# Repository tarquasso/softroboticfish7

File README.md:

***** SETUP *****  
-- This folder should be called /home/pi/softroboticfish7  

===== fish =====  
-- contains code that goes on the Pi in the fish and on the mbed in the fish  

===== controller =====  
-- contains code that goes on the Pi in the acoustic transmitter module (omitted for now in v7)

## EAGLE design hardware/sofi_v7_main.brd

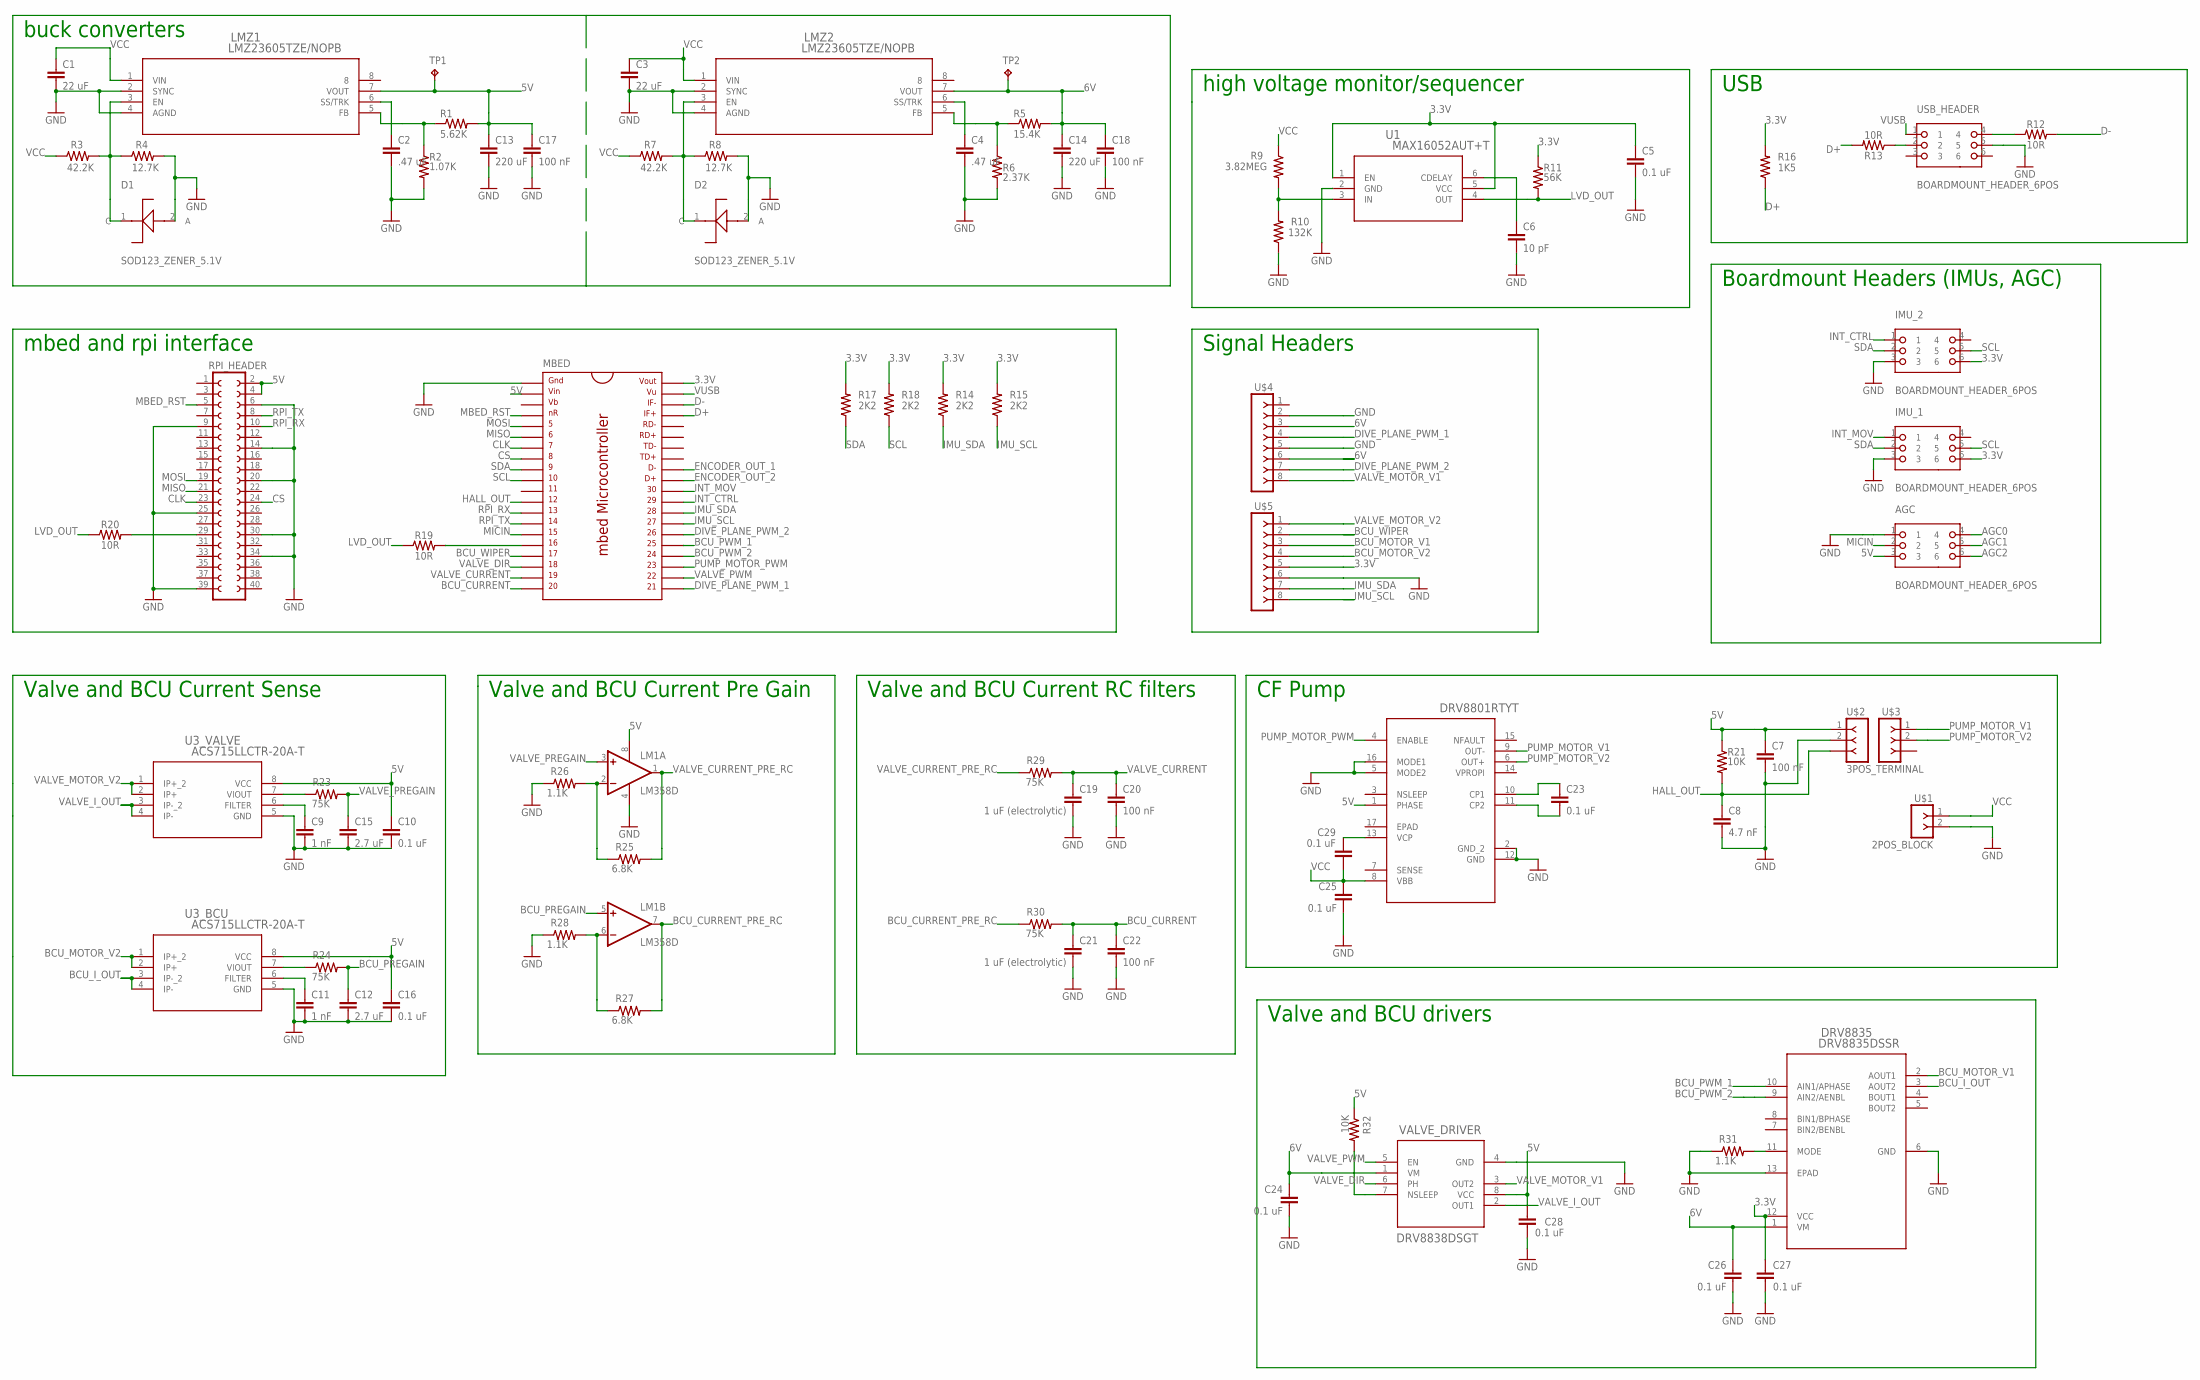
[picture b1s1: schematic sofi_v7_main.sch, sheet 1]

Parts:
AGC: BOARDMOUNT_HEADER_6POS; BOARDMOUNT_HEADER
C1, C3: 22 uF; C0805
C2, C4: .47 uF; C0805
C5, C23, C29: 0.1 uF; C0805
C6: 10 pF; C0603
C7, C17, C18, C20, C22: 100 nF; C0805
C8: 4.7 nF; C0805
C9, C11: 1 nF; C0603
C10, C16, C24, C25, C26, C27, C28: 0.1 uF; C0603
C12, C15: 2.7 uF; C0603
C13, C14: 220 uF; C1206
C19, C21: 1 uF (electrolytic); C0603
D1, D2: SOD123_ZENER_5.1V; SOD123_ZENER
DRV8801: DRV8801RTYT; RTY16
DRV8835: DRV8835DSSR; DSS12_P9X2
IMU_1, IMU_2: BOARDMOUNT_HEADER_6POS; BOARDMOUNT_HEADER
LM1: LM358D; SO08
LMZ1, LMZ2: LMZ23605TZE/NOPB; TZA07A
MBED: MBED_MICROCONTROLLER; DIL40_0.9
R1: 5.62K; M0805
R2: 1.07K; M0805
R3, R7: 42.2K; M0805
R4, R8: 12.7K; M0805
R5: 15.4K; M0805
R6: 2.37K; M0805
R9: 3.82MEG; 0603
R10: 132K; 0603
R11: 56K; R0603
R12, R13, R19, R20: 10R; 0603
R14, R15, R17, R18: 2K2; 0603
R16: 1K5; 0603
R21, R32: 10K; M0805
R23, R24, R29, R30: 75K; M0805
R25, R27: 6.8K; M0805
R26, R28, R31: 1.1K; M0805
RPI_HEADER: FE20-2
TP1, TP2: TPB1,27; B1,27
U1: MAX16052AUT+T; 21-0058I
U3_BCU, U3_VALVE: ACS715LLCTR-20A-T; SOIC-8
U$1: 2POS_BLOCK
U$2, U$3: 3POS_TERMINAL
U$4, U$5: 8POS_TERMINAL
USB_HEADER: BOARDMOUNT_HEADER_6POS; BOARDMOUNT_HEADER
VALVE_DRIVER: DRV8838DSGT; DSG8_P9X1P6

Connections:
3.3V: C5.1, C27.1, DRV8835.12 (VCC), IMU_1.6, IMU_2.6, MBED.40, R11.1, R14.2, R15.2, R16.2, R17.2, R18.2, U1.1 (EN), U1.5 (VCC), U$5.5
5V: AGC.3, C7.1, C10.1, C13.1, C16.1, C17.1, C28.1, DRV8801.1 (PHASE), LM1.8 (V+), LMZ1.7 (VOUT), MBED.2, R1.2, R21.1, R32.1, RPI_HEADER.2, RPI_HEADER.4, TP1.TP, U3_BCU.8 (VCC), U3_VALVE.8 (VCC), U$2.1, VALVE_DRIVER.8 (VCC)
6V: C14.1, C18.1, C24.1, C26.1, DRV8835.1 (VM), LMZ2.7 (VOUT), R5.2, TP2.TP, U$4.3, U$4.6, VALVE_DRIVER.1 (VM)
AGC0: AGC.4
AGC1: AGC.5
AGC2: AGC.6
BCU_CURRENT: C21.1, C22.1, MBED.20, R30.2
BCU_CURRENT_PRE_RC: LM1.7 (OUT), R27.2, R30.1
BCU_I_OUT: DRV8835.3 (AOUT2), U3_BCU.3 (IP-_2), U3_BCU.4 (IP-)
BCU_MOTOR_V1: DRV8835.2 (AOUT1), U$5.3
BCU_MOTOR_V2: U3_BCU.1 (IP+_2), U3_BCU.2 (IP+), U$5.4
BCU_PREGAIN: C12.1, LM1.5 (+IN), R24.2
BCU_PWM_1: DRV8835.10 (AIN1/APHASE), MBED.25
BCU_PWM_2: DRV8835.9 (AIN2/AENBL), MBED.24
BCU_WIPER: MBED.17, U$5.2
CLK: MBED.7, RPI_HEADER.23
CS: MBED.8, RPI_HEADER.24
D+: MBED.37, R13.2, R16.1
D-: MBED.38, R12.2
DIVE_PLANE_PWM_1: MBED.21, U$4.4
DIVE_PLANE_PWM_2: MBED.26, U$4.7
ENCODER_OUT_1: MBED.32
ENCODER_OUT_2: MBED.31
GND: AGC.1, C1.2, C2.2, C3.2, C4.2, C5.2, C6.2, C7.2, C8.2, C9.2, C10.2, C11.2, C12.2, C13.2, C14.2, C15.2, C16.2, C17.2, C18.2, C19.2, C20.2, C21.2, C22.2, C24.2, C25.2, C26.2, C27.2, C28.2, D1.2 (A), D2.2 (A), DRV8801.2 (GND_2), DRV8801.5 (MODE2), DRV8801.12 (GND), DRV8801.16 (MODE1), DRV8835.6 (GND), DRV8835.13 (EPAD), IMU_1.3, IMU_2.3, LM1.4 (V-), LMZ1.2 (SYNC), LMZ1.4 (AGND), LMZ2.2 (SYNC), LMZ2.4 (AGND), MBED.1, R2.2, R4.2, R6.2, R8.2, R10.1, R26.1, R28.1, R31.1, RPI_HEADER.6, RPI_HEADER.9, RPI_HEADER.14, RPI_HEADER.20, RPI_HEADER.25, RPI_HEADER.30, RPI_HEADER.34, RPI_HEADER.39, U1.2 (GND), U3_BCU.5 (GND), U3_VALVE.5 (GND), U$1.2, U$2.2, U$4.2, U$4.5, U$5.6, USB_HEADER.5, VALVE_DRIVER.4 (GND)
HALL_OUT: C8.1, MBED.12, R21.2, U$2.3
IMU_SCL: MBED.27, R15.1, U$5.8
IMU_SDA: MBED.28, R14.1, U$5.7
INT_CTRL: IMU_2.1, MBED.29
INT_MOV: IMU_1.1, MBED.30
LVD_OUT: R11.2, R19.1, R20.1, U1.4 (OUT)
MBED_RST: MBED.4, RPI_HEADER.5
MICIN: AGC.2, MBED.15
MISO: MBED.6, RPI_HEADER.21
MOSI: MBED.5, RPI_HEADER.19
unnamed: R20.2, RPI_HEADER.29
unnamed: C23.1, DRV8801.10 (CP1)
unnamed: LMZ1.5 (FB), R1.1, R2.1
unnamed: R9.2, R10.2, U1.3 (IN)
unnamed: D1.1 (C), LMZ1.3 (EN), R3.2, R4.1
unnamed: C4.1, LMZ2.6 (SS/TRK)
unnamed: LMZ2.5 (FB), R5.1, R6.1
unnamed: C2.1, LMZ1.6 (SS/TRK)
unnamed: C6.1, U1.6 (CDELAY)
unnamed: D2.1 (C), LMZ2.3 (EN), R7.2, R8.1
unnamed: R23.1, U3_VALVE.7 (VIOUT)
unnamed: C9.1, U3_VALVE.6 (FILTER)
unnamed: MBED.16, R19.2
unnamed: R24.1, U3_BCU.7 (VIOUT)
unnamed: C11.1, U3_BCU.6 (FILTER)
unnamed: C23.2, DRV8801.11 (CP2)
unnamed: C29.1, DRV8801.13 (VCP)
unnamed: LM1.2 (-IN), R25.1, R26.2
unnamed: R12.1, USB_HEADER.4
unnamed: LM1.6 (-IN), R27.1, R28.2
unnamed: R13.1, USB_HEADER.2
unnamed: DRV8835.11 (MODE), R31.2
unnamed: R32.2, VALVE_DRIVER.7 (NSLEEP)
PUMP_MOTOR_PWM: DRV8801.4 (ENABLE), MBED.23
PUMP_MOTOR_V1: DRV8801.9 (OUT-), U$3.1
PUMP_MOTOR_V2: DRV8801.6 (OUT+), U$3.2
RPI_RX: MBED.13, RPI_HEADER.10
RPI_TX: MBED.14, RPI_HEADER.8
SCL: IMU_1.5, IMU_2.5, MBED.10, R18.1
SDA: IMU_1.2, IMU_2.2, MBED.9, R17.1
SENSE: DRV8801.7 (SENSE)
VALVE_CURRENT: C19.1, C20.1, MBED.19, R29.2
VALVE_CURRENT_PRE_RC: LM1.1 (OUT), R25.2, R29.1
VALVE_DIR: MBED.18, VALVE_DRIVER.6 (PH)
VALVE_I_OUT: U3_VALVE.3 (IP-_2), U3_VALVE.4 (IP-), VALVE_DRIVER.2 (OUT1)
VALVE_MOTOR_V1: U$4.8, VALVE_DRIVER.3 (OUT2)
VALVE_MOTOR_V2: U3_VALVE.1 (IP+_2), U3_VALVE.2 (IP+), U$5.1
VALVE_PREGAIN: C15.1, LM1.3 (+IN), R23.2
VALVE_PWM: MBED.22, VALVE_DRIVER.5 (EN)
VCC: C1.1, C3.1, C25.1, C29.2, DRV8801.8 (VBB), LMZ1.1 (VIN), LMZ2.1 (VIN), R3.1, R7.1, R9.1, U$1.1
VUSB: MBED.39, USB_HEADER.1

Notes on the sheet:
mbed and rpi interface
buck converters
high voltage monitor/sequencer
Valve and BCU Current RC filters
Valve and BCU Current Pre Gain
Valve and BCU Current Sense
Signal Headers
USB
CF Pump
Valve and BCU drivers
Boardmount Headers (IMUs, AGC)

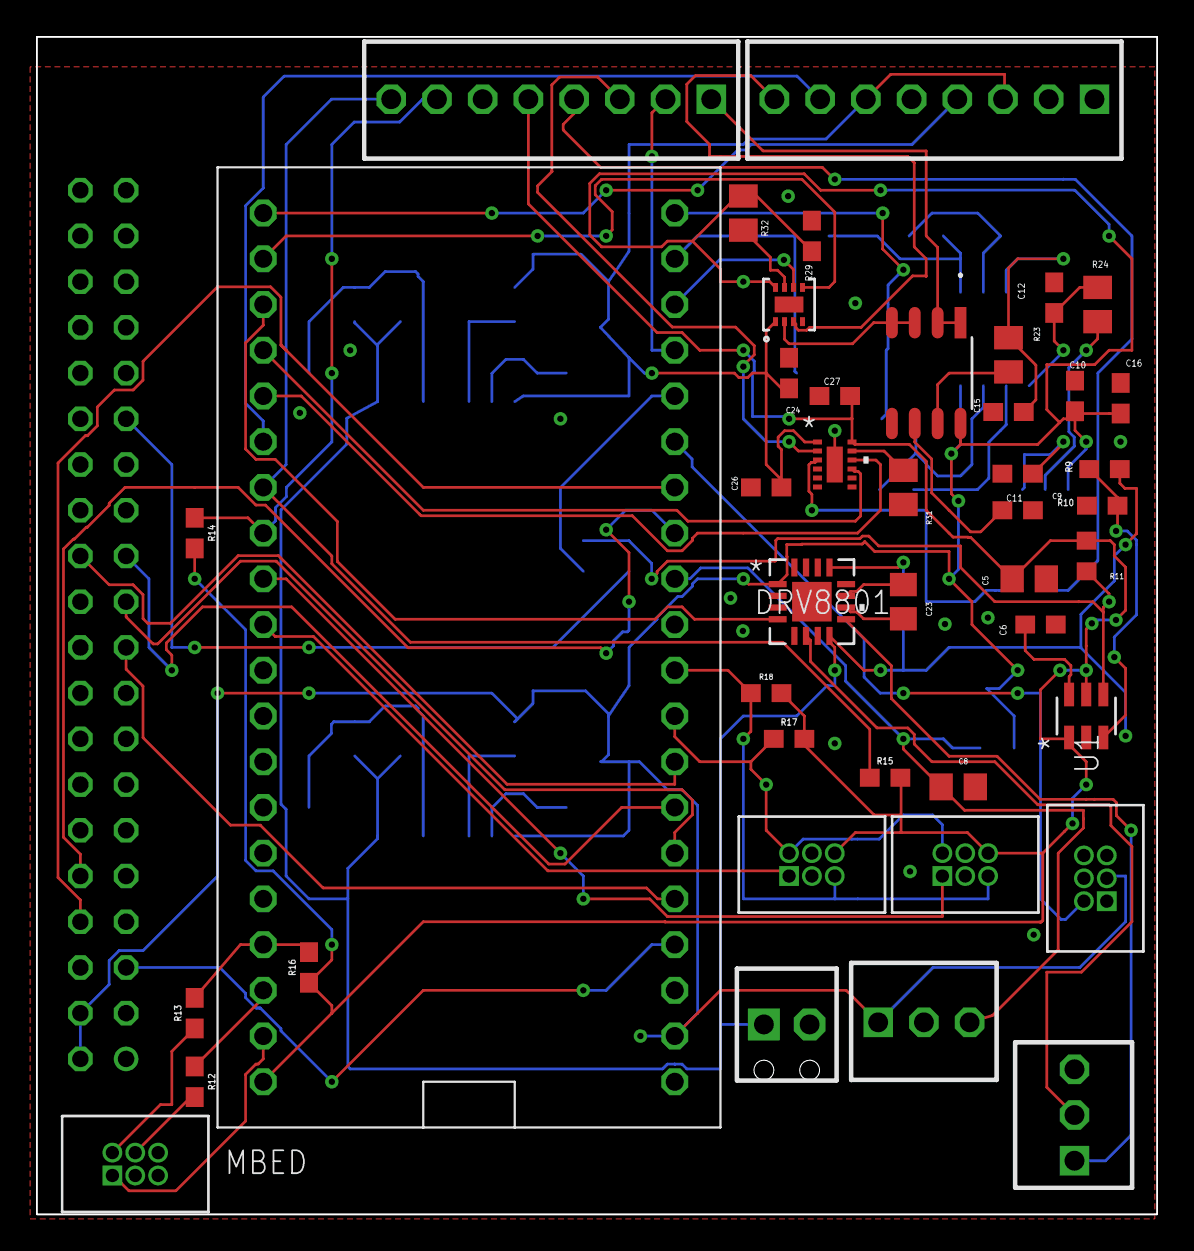
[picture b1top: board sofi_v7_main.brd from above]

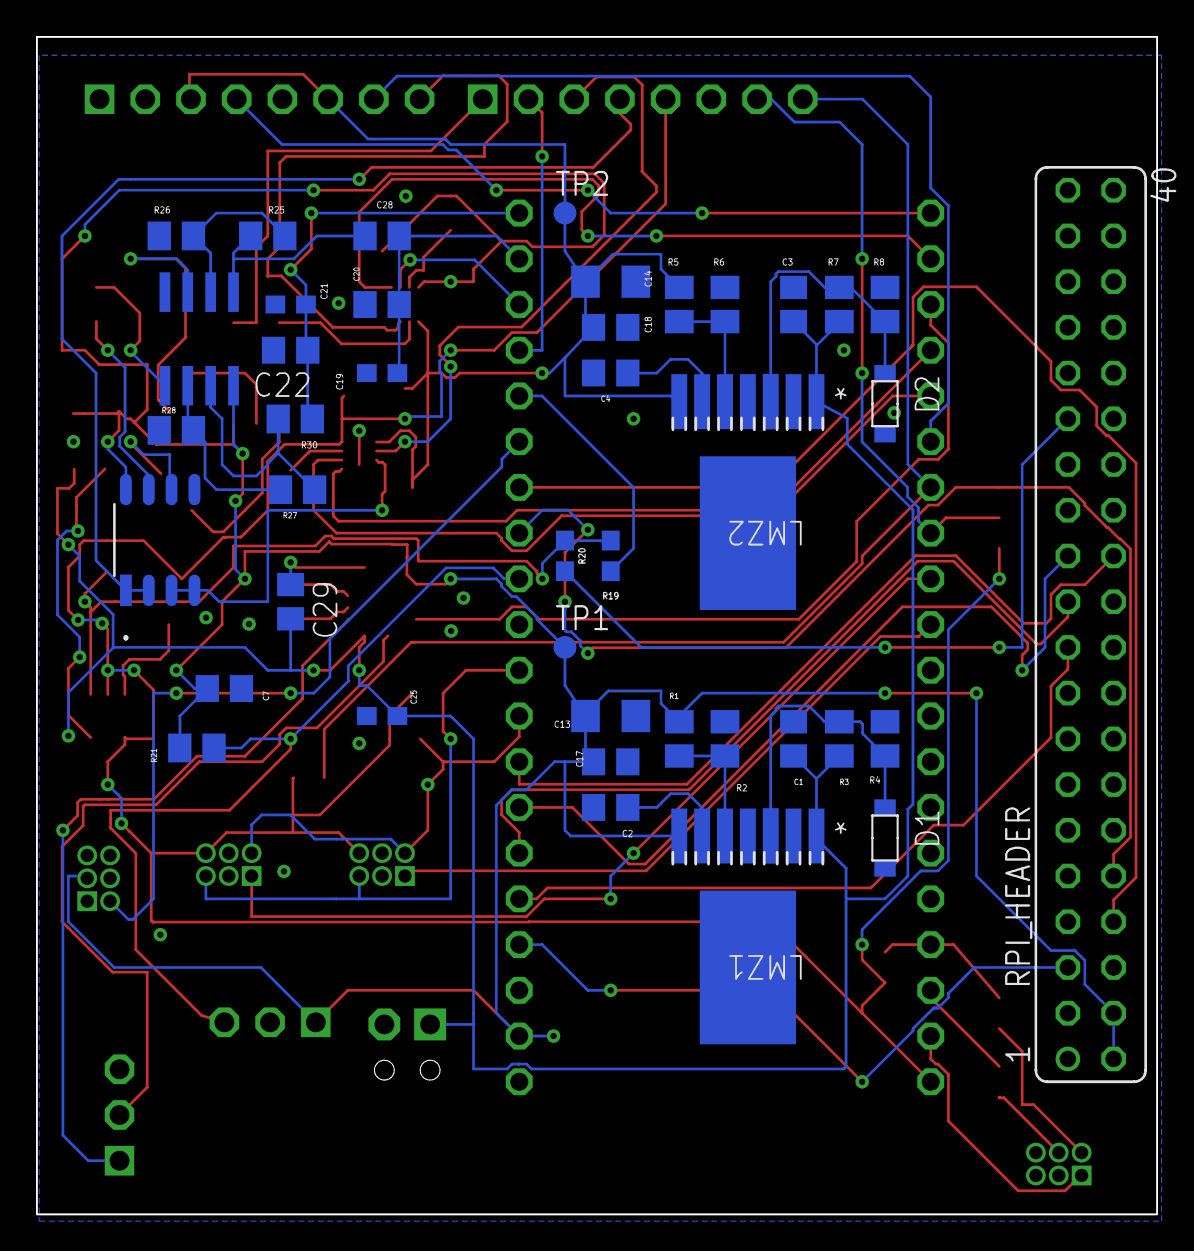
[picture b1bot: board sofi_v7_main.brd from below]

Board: 2 copper layers, 62.2 x 65.4 mm, 84 parts (41 on the bottom side), 69 nets.

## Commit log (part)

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2016-03-05 set up skeleton catkin workspace directory and imported relevant files from softroboticfish4 (but did not yet convert old code to new system setup)
2016-03-08 connected joystick to produce depth, yaw, and speed inputs
2016-03-08 added actual launch and node files
2016-03-12 added freq_ctrl to joystick commands; serial communication functional to light LEDs based on commands in
2016-03-13 switched joystick axes inputs from left is positive to left is negative; removed unused files from fish4_code
2016-03-13 remove .hg folder
2016-03-13 add project file for project
2016-03-14 added lpc expresso project properly, so it can now be imported elsewhere
2016-03-14 added initial versions of BCU and Valve control classes - code compiles but has some warnings; FishController is updated accordingly; ROSControl files in mbed folder is updated but not merged into mb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
2016-03-17 Moving #defines that control modality into individual h files Avoids singleton creation when modalities are disabled
2016-03-17 Adding saved bin files from important experiments
2016-03-18 Adding pi scripts such as volume and view/kill fish processes
2016-03-18 Adding rx startup scripts
2016-03-18 Adding RX python scripts
2016-03-18 Organizing and restructuring all files
2016-03-18 Making scripts executable
2016-03-18 Updating Pi scripts
2016-03-18 Editing readme files to try to have github show line breaks
2016-03-18 make debug build on mbed
2016-03-19 activate serial controller, deactivate acoustic controller
2016-03-19 Refactor FishController to searate fish 4 and fish 6
2016-03-19 - reimplemented valve with pump control - version based on cyndia's approach. this approach saturates - changed name of bcu class
2016-03-19 PumpWithValve: updated yaw method
2016-03-19 add imu and pressure sensor
2016-04-13 added basic tests for valve (freq and yaw input) and bcu to move motors based on keyboard commands and hall/pressure sensor readings
2016-05-01 added project to experiment with BCU input voltage and resultant motor current & encoder positions made superficial changes to PumpWithValve class added PID control loops via pressure and encoder sen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
2016-05-04 added base timing test for just the pressure sensor (BCU_Test/main.cpp); test for the BCU moved to main_real.txt finished testing the added failsafe for the Valve
2016-06-10 adding header files for msgs
2016-06-10 fixed a lot about depth_control
2016-06-15 Added very basic IMU Test
2016-06-16 first commit for branch. Tried to bring in the last couple changes to master into dev, as well as a basic IMU_Test.
2016-06-20 Added basic serial bin for mbed. Counts down binary and sends BOOM string via rosserial
2016-06-21 Fixed folder structure of basic serial test
2016-06-27 trying to fix CMakeLists in the old ros
2016-06-27 fixing dependencies
2016-06-27 fixed dep with depthcontrol
2016-06-27 whoops. fixed Cmake portion of dep issue with depth control
2016-06-28 first compile attempt
2016-06-28 fixed defaults
2016-06-28 improved gitignore
2016-06-28 improved gitignore again
2016-06-28 add gcc ar o files
2016-06-28 hopefully fixed axes issue
2016-06-28 fixed modes
2016-06-28 fixed axes
2016-06-28 fixed last mode
2016-06-28 add gitignnore
2016-06-28 libraries for buoyancy control unit
2016-06-28 main files for buyancy control unit
2016-06-28 lpc expresso mbed folder
2016-06-28 add ing project files for lpcex
2016-06-28 add gitignore
2016-06-29 working mbed side of depth test
2016-06-29 remove some unnecessary files
2016-06-29 updated project files
2016-06-29 remove more debug files
2016-06-30 Position control working
2016-06-30 Cleaned up
2016-06-30 cleanup
2016-06-30 add MODSERIAL to buyancy test unit
2016-06-30 add serialcomm and modeserial to buoyancy test
2016-06-30 remove ros lib release
2016-06-30 remove unnecessary files
2016-06-30 commit line ending changes
2016-06-30 add gitignore to roboticfish6
2016-06-30 update project file
2016-06-30 fix depth test to compile
2016-06-30 make depth test compilable in lpcexpresso
2016-06-30 Made ticker to work with potentiometer controls for gains
2016-07-01 BTU changes for memeber variabkle renaming
2016-07-01 renaming #defines
2016-07-01 serial comm addition
2016-07-01 update modserial
2016-07-01 set up for testing
2016-07-01 Non static single ticker version of the btu, ready for plugin.
2016-07-01 buoyancy test unit now linking to static lib
2016-07-01 added servo option and depth to pressure conversion
2016-07-01 remove libs from depth test
2016-07-02 minor calculation fix
2016-07-03 buoyancy_test_unit_servo
2016-07-03 add btu to libs
2016-07-03 updated bcu test projects
2016-07-03 btu servo release version compiles
2016-07-03 add position reading and store position value to servo class
2016-07-03 calibrated position controller for btu
2016-07-04 working on pressure sensor reading, mbed not starting up
2016-07-04 updated project settings
2016-07-04 remove waits from MS5837 pressure unit library
2016-07-04 add time step minimum
2016-07-05 created call to controller.
2016-07-05 cleared out BTU folder in Depth_Test
2016-07-05 add bias to make the pid controller workable
2016-07-05 added security to pressure sensor
2016-07-05 set value to zero and add printf to the main
2016-07-05 btu: get pressure reading at start
2016-07-05 ready for second pool test
2016-07-05 code used for experiment
2016-07-05 Added anti-reset-windup to compute()
2016-07-06 Added anti-reset windup
2016-07-06 changed depth_test to use new BTU lite
2016-07-06 fixed bad naming, calls of getPressureReading
2016-07-06 fixed encapsulation of btu lite
2016-07-07 fixed several bugs in PID, BTU
2016-07-07 fixed scaling on rpi side
2016-07-07 fixed default mode on pi side
2016-07-07 working pcSerial based test
2016-07-07 working buoyancy test for pool
2016-07-07 updated servo values
2016-07-08 added serial logging scripts
2016-07-08 last minute improvement in logging
2016-07-11 added mission mode code
2016-07-11 started writing for Actuator
2016-07-11 added logging
2016-07-12 made multi depth missions work
2016-07-13 fixed various bugs in mission control
2016-07-13 pool ready mission control
2016-07-14 fixed no debrief after timeout bug
2016-07-14 pool ready mission btu
2016-07-15 project files
2016-07-15 added SMA filter and mission code for actuator
2016-07-15 better default value
2016-07-18 small updates
2016-07-18 update mbed libs cproject
2016-07-19 fixed printf
2016-07-19 added master-slave to BtuLinear. Commented out clip
2016-07-19 fixed naming problems
2016-07-19 fix project warnings for missing include paths
2016-07-19 moving window temp removed
2016-07-19 fixed vel control edge cases'
2016-07-19 make time step 3 times the pressure sensor time step fix moving average pointer bug
2016-07-19 pressure sensor working
2016-07-19 remove binary
2016-07-19 add #defines
2016-07-19 clipped commandable voltage
2016-07-19 doing some cleanup, reorganization
2016-07-19 more cleanup
2016-07-19 moved BCU_Test to Deprecated
2016-07-19 shifting around folders
2016-07-19 completing the shuffle
2016-07-19 cleared up IMU_Test moving
2016-07-20 updated btu code
2016-07-20 remove pi_clip and replace with utility
2016-07-20 only reformat PID Controller code, no functionality change
2016-07-20 fix gain names in PID Controller cLASS
2016-07-20 update utility
2016-07-20 speed up compute step of PID Controller
2016-07-20 fix minor bug with btu linear
2016-07-20 rename variables in PID Controller
2016-07-21 set position control to use voltage
2016-07-21 add position control code using voltage
2016-07-21 depth controller now velocity based
2016-07-21 moved clipping and other checks to voltage control
2016-07-21 voltage control using correct updated variable for command now
2016-07-21 rename two local variables
2016-07-21 changing back to local floats
2016-07-21 changing back to local floats (reverted from commit af8a5c95ca4f8792d58ba17b3be1e454d5687c94)
2016-07-21 BtuLinear with Actuator class
2016-07-21 fixed wrong name for getting tunings within the main.cpp files of mission control and actuator control
2016-07-21 fixed tuning names to be consistent witrh nomenclature
2016-07-21 added dry run support
2016-07-21 compiling version of dry run support
2016-07-21 commented actuator code
2016-07-21 first draft of btu_act_combo. Compiles, but is untested
2016-07-21 code changes from experiment
2016-07-22 changed potentiometer pin
2016-07-22 add gitignores
2016-07-22 add position controller tunings
2016-07-22 reformatting code
2016-07-22 actuator class with moving average and simplified position min max
2016-07-22 working btu_act_combo
2016-07-22 fixed loop freezing issue
2016-07-22 added cyclic actuator test project and library file
2016-07-25 add gitignor for cycliuca ctuator
2016-07-25 add ref for cyclic actuator
2016-07-26 tweaked PID Position controller so it goes smoothly to the boundaries
2016-07-28 added script to debug hardware. also debugging scanf, printf
2016-07-28 changed velocity to voltage control
2016-07-28 good log with good gains
2016-08-01 added logs and curating script
2016-08-01 added the pool logs from today
2016-08-02 plotted pool testing and negated depth error
2016-08-02 cleaned up log folders a bit
2016-08-08 updated linear libraries and added servo version
2016-08-08 fixed a lot of rosserial stuff
2016-08-08 fixed depth control bug
2016-08-12 prepped for vv control
2016-08-17 pump AM control added
2016-08-17 loggssss
2016-08-22 added javadoc style docs to Btu
2016-08-23 fixes
2016-08-25 control for whole fish
2016-09-06 for pool test, accel control
2016-10-27 opencv links with camera package
2016-11-02 Camera pub and sub working
2016-11-04 Tested camera successfully with avg RGB values
2016-11-14 Camera driver
2016-12-09 fixed raspicam speed
2017-01-11 pin vor valve changes
2017-01-12 gitignore for compiled files; remove ros_lib
2017-01-12 Removed old camera package
2017-01-17 Revert rosserial_test to use existing msg
2017-01-17 No longer track build files for serial_test
2017-01-17 gitignore built files
2017-01-18 Fix bug in quaternion constructor
2017-01-18 Remove temperature to save buffer space
2017-01-18 Increase baud rate
2017-01-20 IMU test with new library, uses gcc4mbed
2017-01-23 Library to coordinate asynchronous access to I2C
2017-01-23 updated imu_test
2017-01-23 I2CManager can send command bytes; pressure sensor library uses I2CManager; test updated
2017-01-23 Removed serial print from I2CManager
2017-01-23 MBED collects IMU and pressure data simultaneously and publishes over ROS
2017-01-26 Apriltags library doesn't need to flip
2017-01-31 Minimal camera pipeline package
2017-03-16 OpenCV subdivided thresholding tester
2017-03-16 Matlab scripts to generate HSV histogram and print as a c array literal
2017-03-21 Added reference caps from videos, relevant crops
2017-03-21 Added relevant crops
2017-03-23 Updated corner detection algorithm
2017-04-13 Removed hard-coded pathnames; added instructions for running the line detection script
2019-06-24 Rename sofi_v7_main.brd to hardware/sofi_v7_main.brd
2019-06-24 Rename sofi_v7_main.sch to hardware/sofi_v7_main.sch
2019-07-31 Update BluetoothJoystickController.py
    Tweaked update interval for mbed, bytearray structure and null termination
2019-07-31 Update FishJoystick.py
    Tweaked null termination and default controller setting
2019-08-07 Removed use of bcuPWMPin because of new driver
2019-08-07 Updated pin assignments for new board
2019-08-14 added BCU debug printf
2019-08-14 Added debugBCUControl
2019-08-14 Added BCU debugging helper funcs
2019-08-14 Modified control law ranges, input depth range
2019-08-19 Added debugSensor
2019-08-19 Added readPressure
2019-08-19 Added mbed repo for SoFi 7 preliminary code
2019-08-21 included dive plane control in Fish6
2019-08-21 Uncommented programming, serial logging, added &
2019-10-06 Create test
2019-10-06 Added test.py
2019-10-06 Fixed ASCII error in FishJoystick.py
2019-10-06 Changed folder structure for data logs
2019-12-03 new blob_detector that prints centroids, detects larger objects
2020-01-29 added test controller
2020-02-27 added AutoController.py
2020-02-27 added recordings folder

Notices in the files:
parts and their libraries:
SparkFun-Resistors: Licensing: Creative Commons ShareAlike 4.0 International - https://creativecommons.org/licenses/by-sa/4.0
